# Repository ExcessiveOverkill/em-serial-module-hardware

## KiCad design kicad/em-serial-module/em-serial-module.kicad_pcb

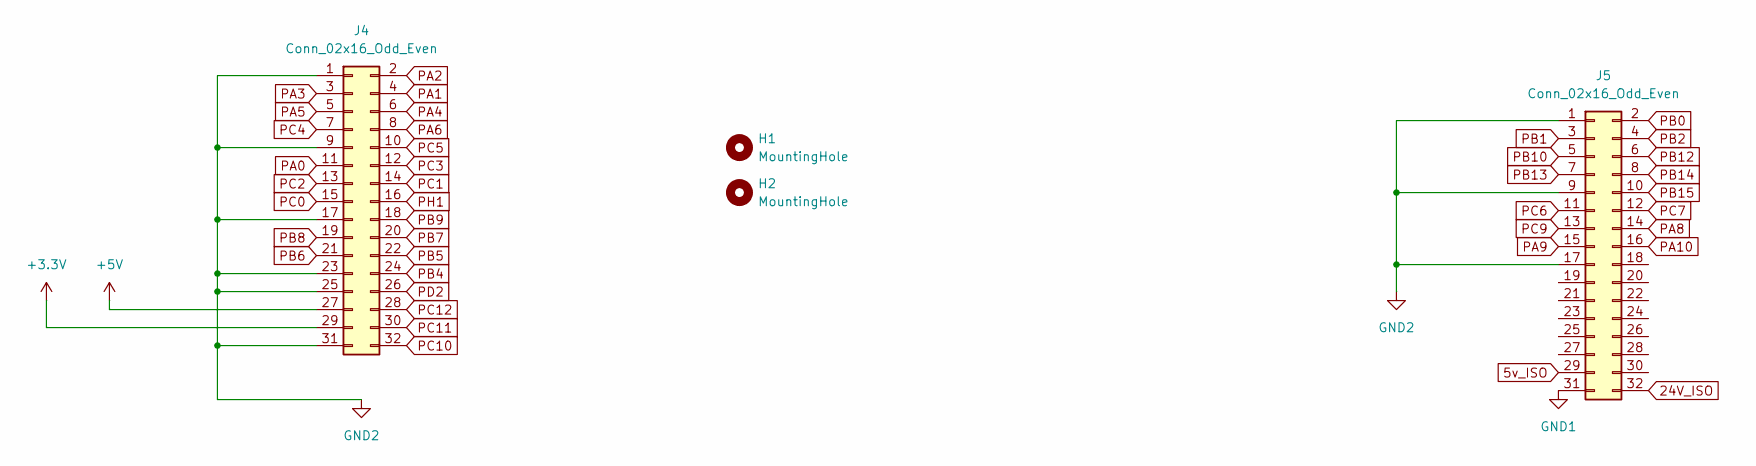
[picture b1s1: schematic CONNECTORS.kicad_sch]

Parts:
H1, H2: MountingHole; MountingHole_3.2mm_M3
J4, J5: Conn_02x16_Odd_Even; PinHeader_2x16_P2.54mm_Vertical

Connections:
5v_ISO: J5.29; also elsewhere on the board
24V_ISO: J5.32; also elsewhere on the board
+3.3V: J4.29; also elsewhere on the board
+5V: J4.27; also elsewhere on the board
GND1: J5.31; also elsewhere on the board
GND2: J4.1, J4.9, J4.17, J4.23, J4.25, J4.31, J5.1, J5.9, J5.17; also elsewhere on the board
PA0: J4.11; also elsewhere on the board
PA1: J4.4; also elsewhere on the board
PA2: J4.2; also elsewhere on the board
PA3: J4.3; also elsewhere on the board
PA4: J4.6; also elsewhere on the board
PA5: J4.5; also elsewhere on the board
PA6: J4.8; also elsewhere on the board
PA8: J5.14; also elsewhere on the board
PA9: J5.15; also elsewhere on the board
PA10: J5.16; also elsewhere on the board
PB0: J5.2; also elsewhere on the board
PB1: J5.3; also elsewhere on the board
PB2: J5.4; also elsewhere on the board
PB4: J4.24; also elsewhere on the board
PB5: J4.22; also elsewhere on the board
PB6: J4.21; also elsewhere on the board
PB7: J4.20; also elsewhere on the board
PB8: J4.19; also elsewhere on the board
PB9: J4.18; also elsewhere on the board
PB10: J5.5; also elsewhere on the board
PB12: J5.6; also elsewhere on the board
PB13: J5.7; also elsewhere on the board
PB14: J5.8; also elsewhere on the board
PB15: J5.10; also elsewhere on the board
PC0: J4.15; also elsewhere on the board
PC1: J4.14; also elsewhere on the board
PC2: J4.13; also elsewhere on the board
PC3: J4.12; also elsewhere on the board
PC4: J4.7; also elsewhere on the board
PC5: J4.10; also elsewhere on the board
PC6: J5.11; also elsewhere on the board
PC7: J5.12; also elsewhere on the board
PC9: J5.13; also elsewhere on the board
PC10: J4.32; also elsewhere on the board
PC11: J4.30; also elsewhere on the board
PC12: J4.28; also elsewhere on the board
PD2: J4.26; also elsewhere on the board
PH1: J4.16; also elsewhere on the board

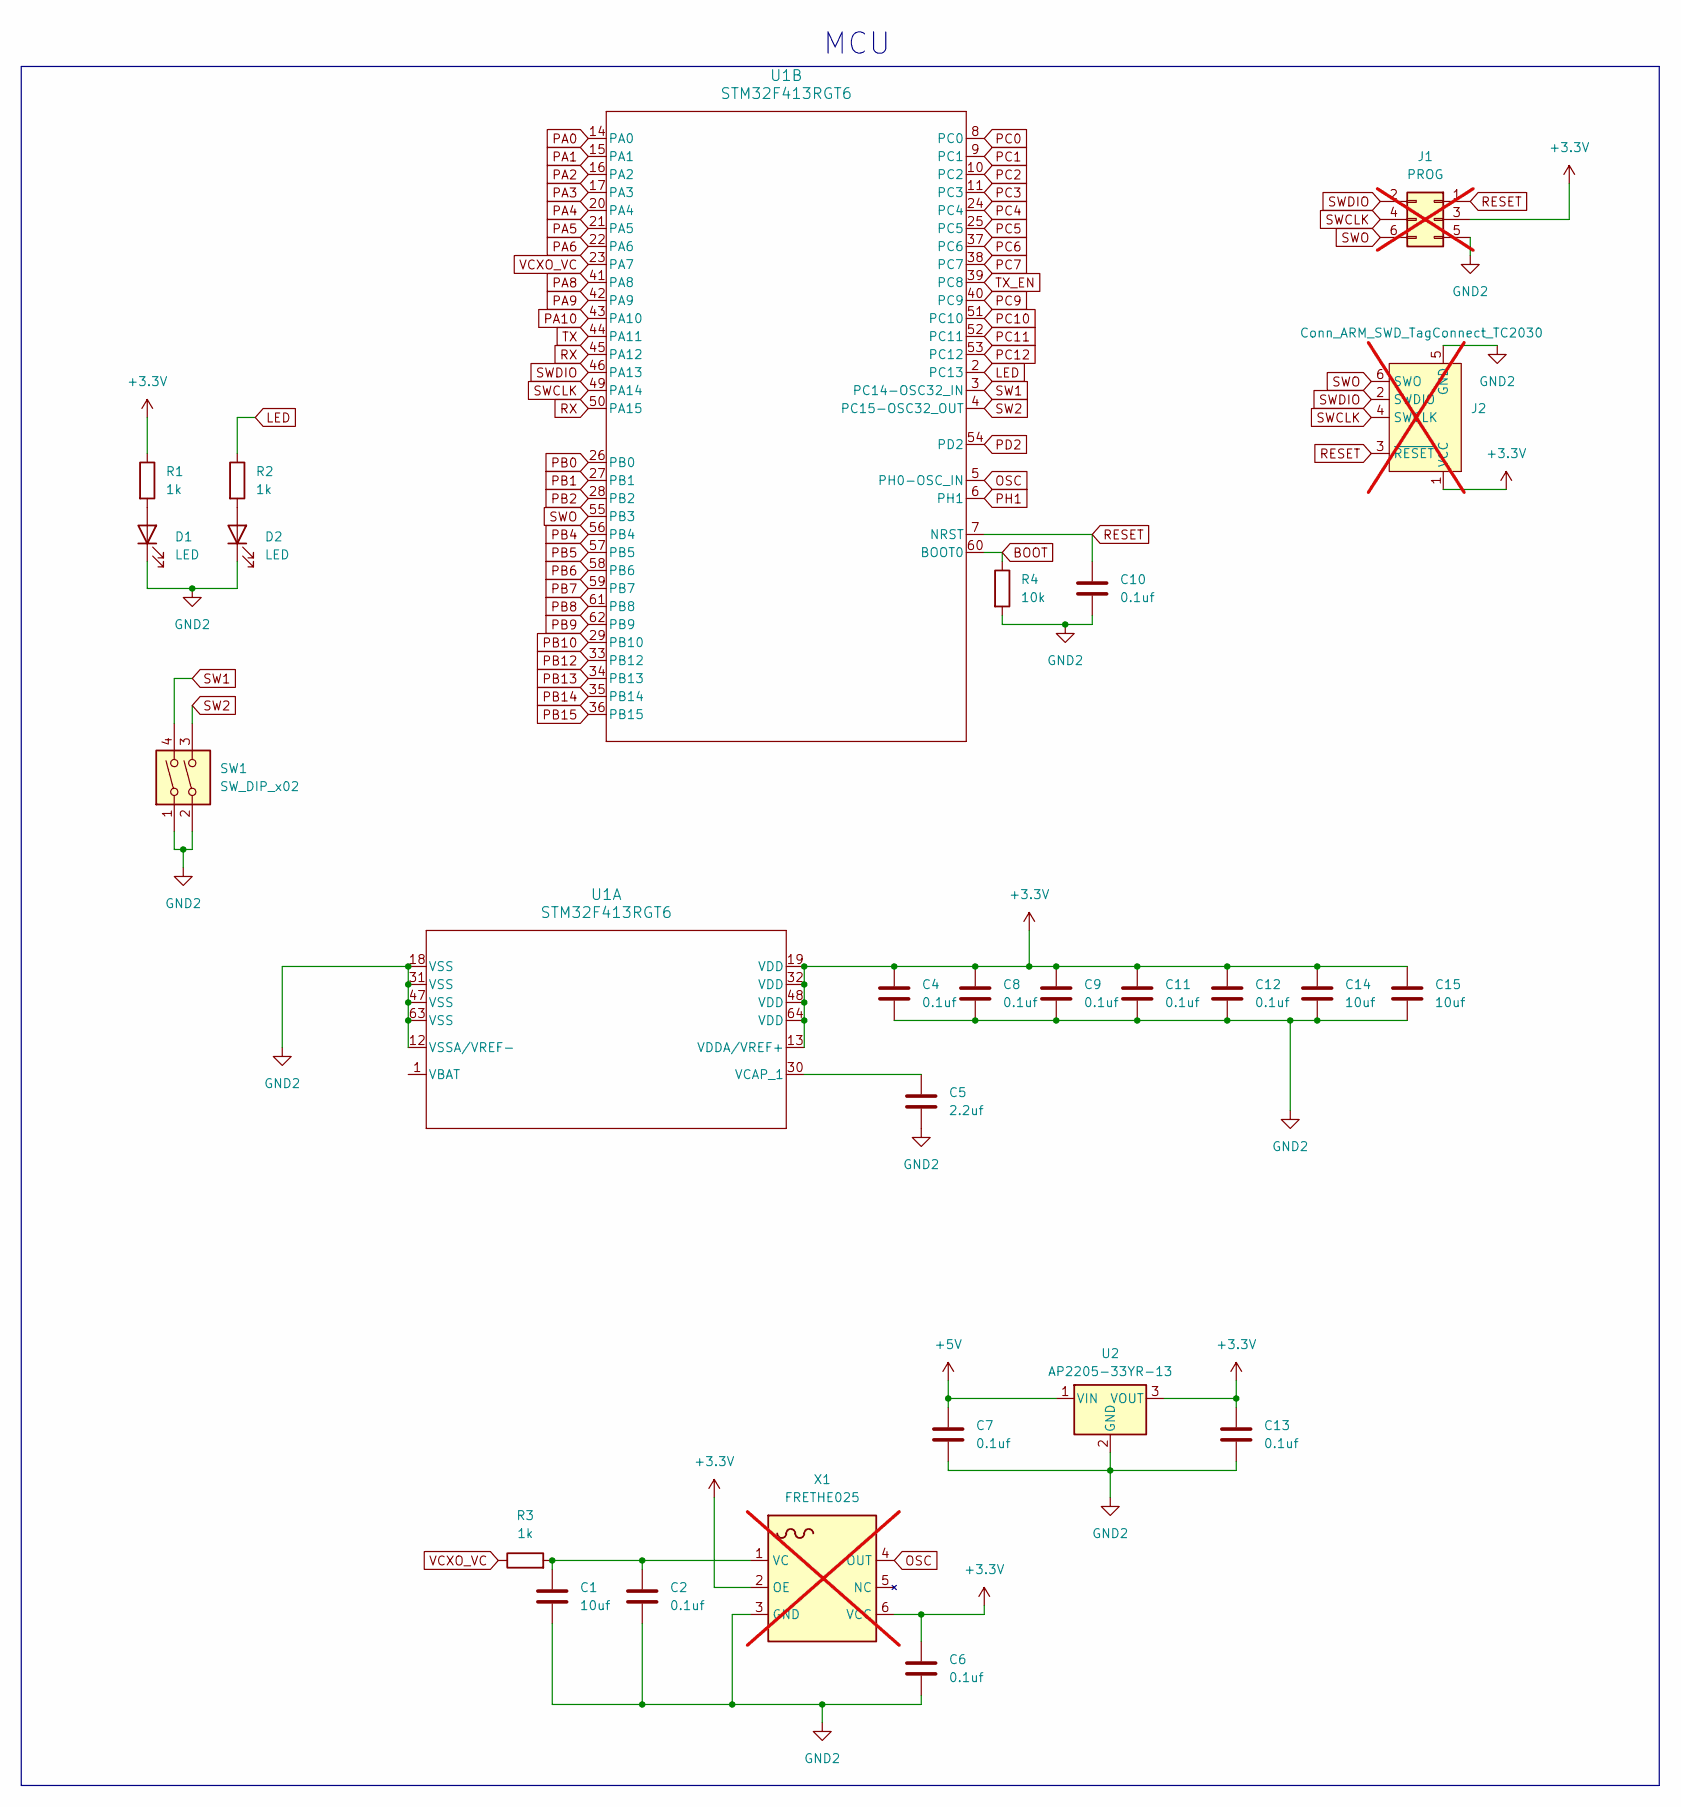
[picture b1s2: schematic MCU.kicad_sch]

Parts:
C1, C14, C15: 10uf; C_0805_2012Metric; Part number GRM21BR61H106KE43L
C2, C4, C6, C7, C8, C9, C10, C11, C12, C13: 0.1uf; C_0603_1608Metric; Part number CC0603ZRY5V9BB104
C5: 2.2uf; C_0603_1608Metric; Part number CL10A105KB8NNNC
D1, D2: LED; LED_0603_1608Metric
J1: PROG; PinHeader_2x03_P2.54mm_Vertical; not fitted
J2: Conn_ARM_SWD_TagConnect_TC2030; Tag-Connect_TC2030-IDC-FP_2x03_P1.27mm_Vertical; not fitted
R1, R2: 1k; R_0603_1608Metric
R3: 1k; R_0603_1608Metric; Part number RC0603FR-071KL
R4: 10k; R_0603_1608Metric; Part number RC0603FR-0710KL
SW1: SW_DIP_x02; DS04-254-2-02BK-SMT_CUD
U1: STM32F413RGT6; LQFP64-10x10mm; Part number STM32F413RGT6
U2: AP2205-33YR-13; SOT-89-3; Part number AP2205-33YR-13
X1: FRETHE025; FR_3-3V; Part number FRETHE025; not fitted

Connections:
+3.3V: C4.1, C6.1, C8.1, C9.1, C11.1, C12.1, C13.1, C14.1, C15.1, J1.3, J2.1 (VCC), R1.1, U1.13 (VDDA/VREF+), U1.19 (VDD), U1.32 (VDD), U1.48 (VDD), U1.64 (VDD), U2.3 (VOUT), X1.2 (OE), X1.6 (VCC); also elsewhere on the board
+5V: C7.1, U2.1 (VIN); also elsewhere on the board
BOOT: R4.1, U1.60 (BOOT0)
GND2: C1.2, C2.2, C4.2, C5.2, C6.2, C7.2, C8.2, C9.2, C10.2, C11.2, C12.2, C13.2, C14.2, C15.2, D1.1 (K), D2.1 (K), J1.5, J2.5 (GND), R4.2, SW1.1, SW1.2, U1.12 (VSSA/VREF-), U1.18 (VSS), U1.31 (VSS), U1.47 (VSS), U1.63 (VSS), U2.2 (GND), X1.3 (GND); also elsewhere on the board
LED: R2.1, U1.2 (PC13)
unnamed: D1.2 (A), R1.2
unnamed: D2.2 (A), R2.2
unnamed: C5.1, U1.30 (VCAP_1)
unnamed: C1.1, C2.1, R3.2, X1.1 (VC)
OSC: U1.5 (PH0-OSC_IN), X1.4 (OUT)
PA0: U1.14 (PA0); also elsewhere on the board
PA1: U1.15 (PA1); also elsewhere on the board
PA2: U1.16 (PA2); also elsewhere on the board
PA3: U1.17 (PA3); also elsewhere on the board
PA4: U1.20 (PA4); also elsewhere on the board
PA5: U1.21 (PA5); also elsewhere on the board
PA6: U1.22 (PA6); also elsewhere on the board
PA8: U1.41 (PA8); also elsewhere on the board
PA9: U1.42 (PA9); also elsewhere on the board
PA10: U1.43 (PA10); also elsewhere on the board
PB0: U1.26 (PB0); also elsewhere on the board
PB1: U1.27 (PB1); also elsewhere on the board
PB2: U1.28 (PB2); also elsewhere on the board
PB4: U1.56 (PB4); also elsewhere on the board
PB5: U1.57 (PB5); also elsewhere on the board
PB6: U1.58 (PB6); also elsewhere on the board
PB7: U1.59 (PB7); also elsewhere on the board
PB8: U1.61 (PB8); also elsewhere on the board
PB9: U1.62 (PB9); also elsewhere on the board
PB10: U1.29 (PB10); also elsewhere on the board
PB12: U1.33 (PB12); also elsewhere on the board
PB13: U1.34 (PB13); also elsewhere on the board
PB14: U1.35 (PB14); also elsewhere on the board
PB15: U1.36 (PB15); also elsewhere on the board
PC0: U1.8 (PC0); also elsewhere on the board
PC1: U1.9 (PC1); also elsewhere on the board
PC2: U1.10 (PC2); also elsewhere on the board
PC3: U1.11 (PC3); also elsewhere on the board
PC4: U1.24 (PC4); also elsewhere on the board
PC5: U1.25 (PC5); also elsewhere on the board
PC6: U1.37 (PC6); also elsewhere on the board
PC7: U1.38 (PC7); also elsewhere on the board
PC9: U1.40 (PC9); also elsewhere on the board
PC10: U1.51 (PC10); also elsewhere on the board
PC11: U1.52 (PC11); also elsewhere on the board
PC12: U1.53 (PC12); also elsewhere on the board
PD2: U1.54 (PD2); also elsewhere on the board
PH1: U1.6 (PH1); also elsewhere on the board
RESET: C10.1, J1.1, J2.3 (~RESET), U1.7 (NRST)
RX: U1.45 (PA12), U1.50 (PA15); also elsewhere on the board
SW1: SW1.4, U1.3 (PC14-OSC32_IN)
SW2: SW1.3, U1.4 (PC15-OSC32_OUT)
SWCLK: J1.4, J2.4 (SWCLK), U1.49 (PA14)
SWDIO: J1.2, J2.2 (SWDIO), U1.46 (PA13)
SWO: J1.6, J2.6 (SWO), U1.55 (PB3)
TX: U1.44 (PA11); also elsewhere on the board
TX_EN: U1.39 (PC8); also elsewhere on the board
VCXO_VC: R3.1, U1.23 (PA7)

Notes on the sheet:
MCU

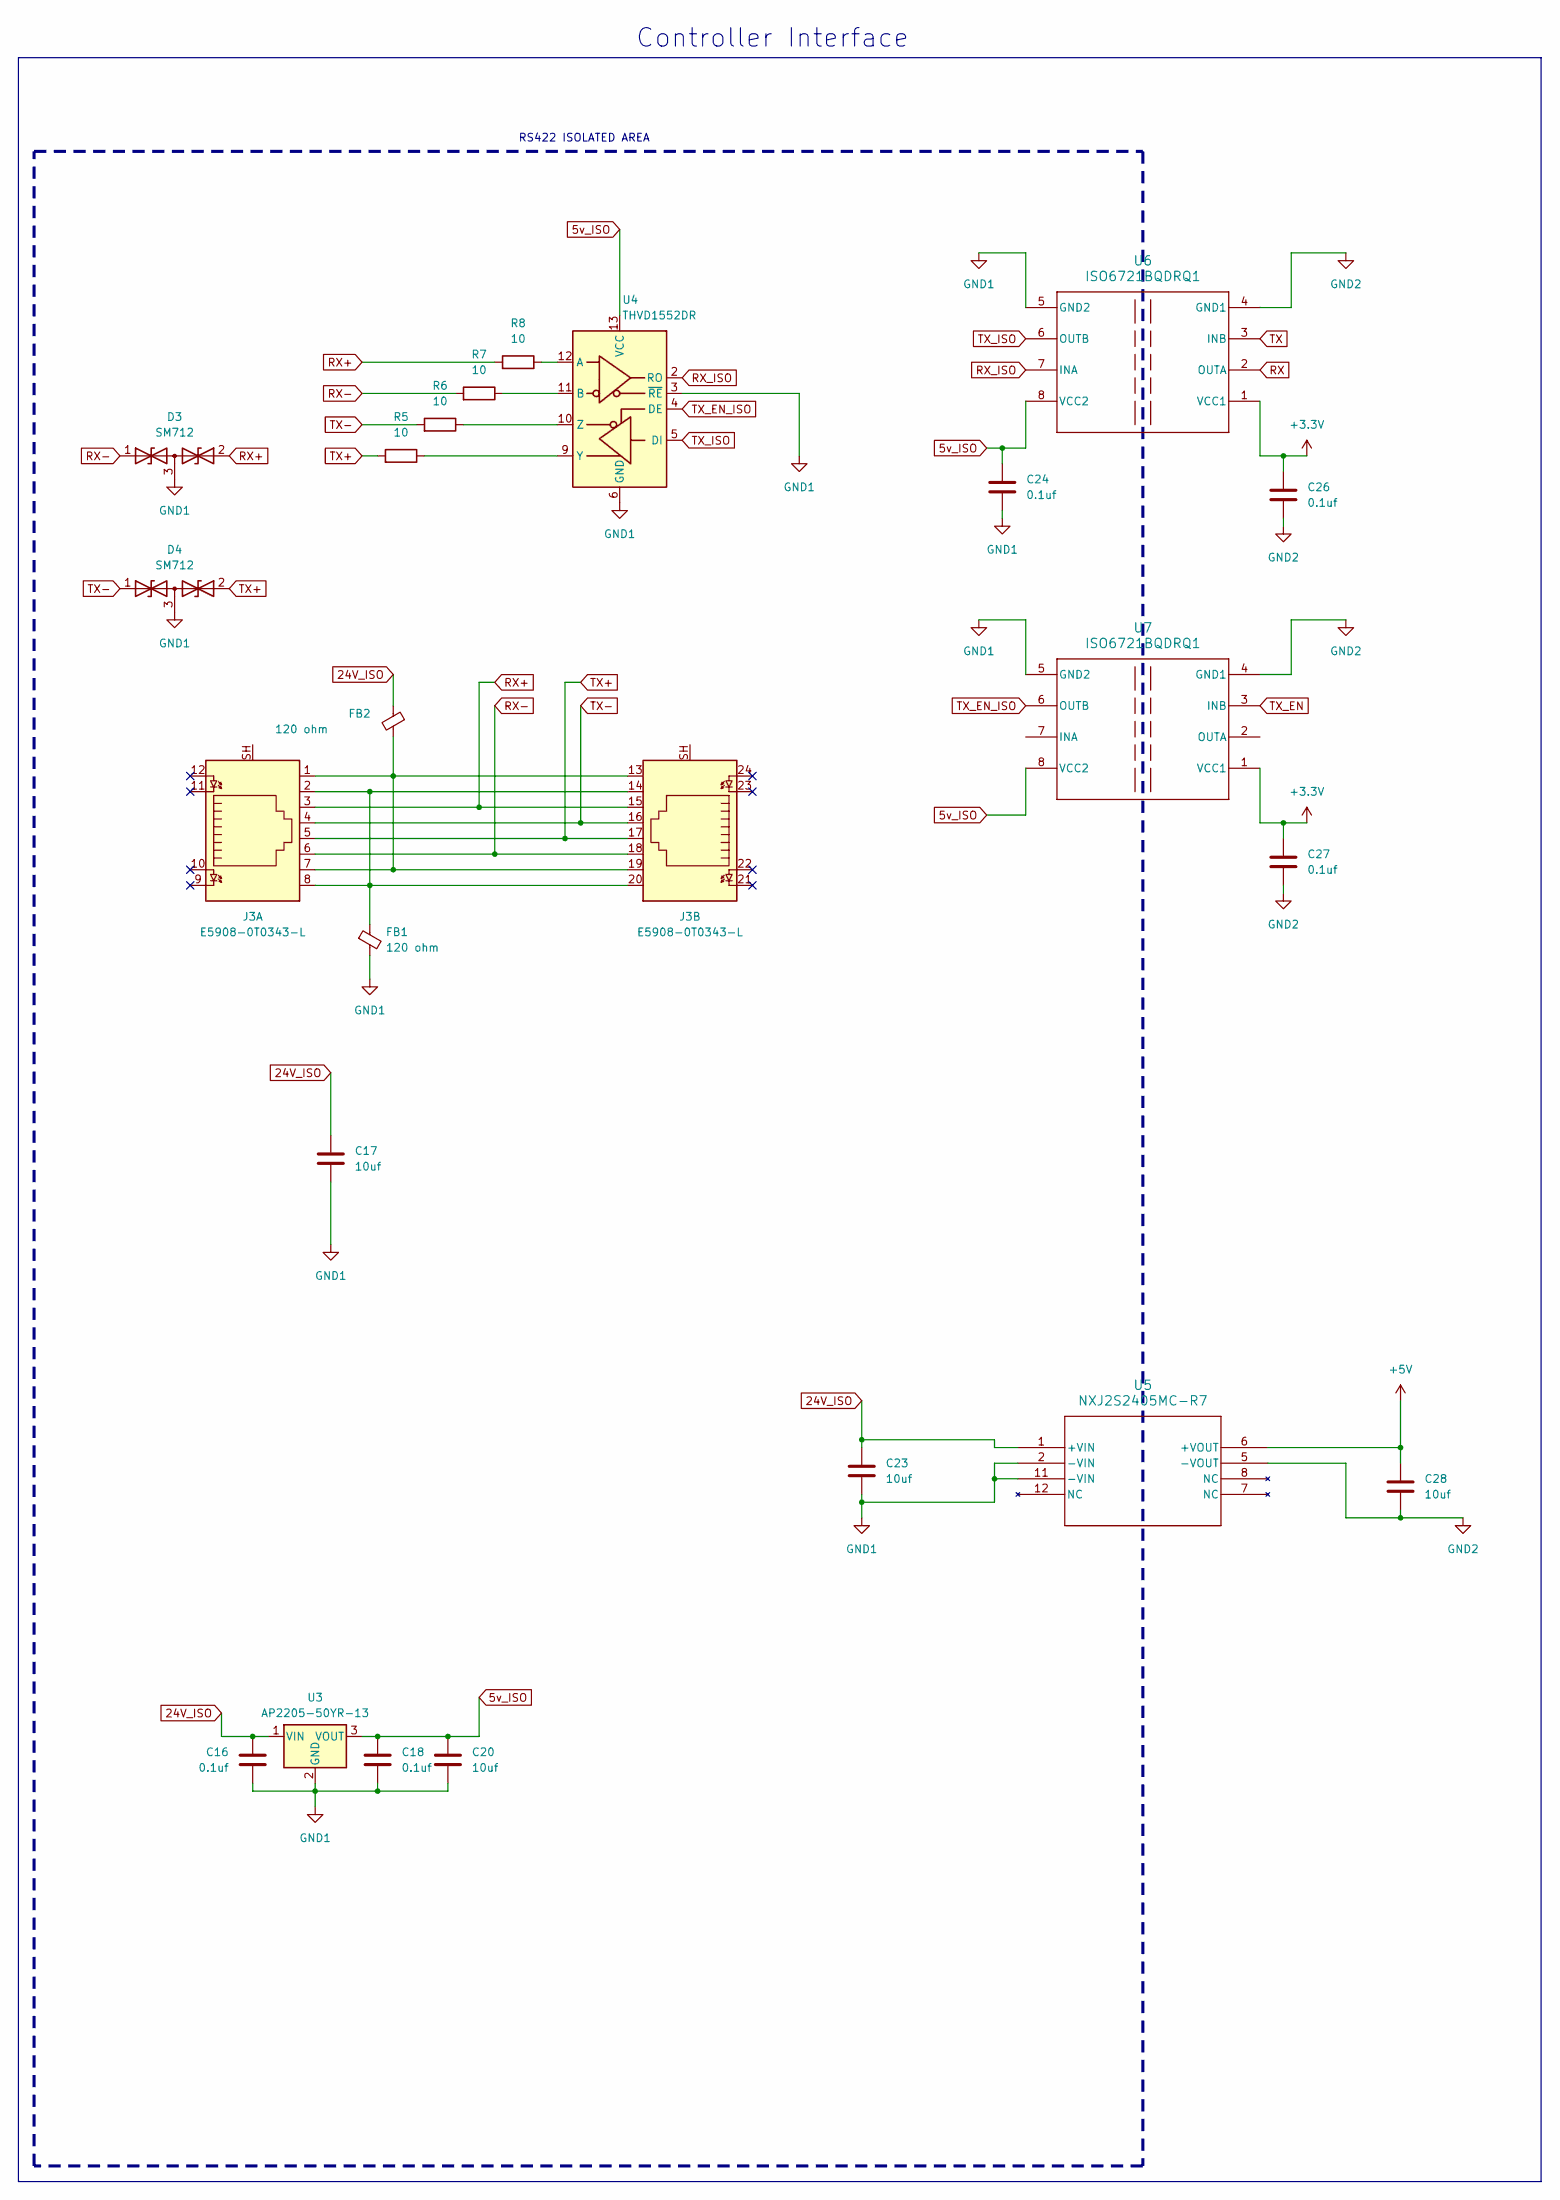
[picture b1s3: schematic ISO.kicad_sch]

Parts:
C16, C18, C24, C26, C27: 0.1uf; C_0603_1608Metric; Part number CC0603ZRY5V9BB104
C17, C20, C23, C28: 10uf; C_0805_2012Metric; Part number GRM21BR61H106KE43L
D3, D4: SM712; SOT-23; Part number SM712
FB1, FB2: 120 ohm; L_0603_1608Metric; Part number LI0603G121R-10
J3: E5908-0T0343-L; RJ45_E5908-0T0343-L; Part number E5908-0T0343-L
R5, R6, R7, R8: 10; R_0603_1608Metric; Part number RMCF0603FT10R0
U3: AP2205-50YR-13; SOT-89-3; Part number AP2205-50YR-13
U4: THVD1552DR; SOIC-14_3.9x8.7mm_P1.27mm; Part number THVD1552DR
U5: NXJ2S2405MC-R7; NXJ2_24V_MUR; Part number NXJ2S2415MC-R7
U6, U7: ISO6721BQDRQ1; SOICN-8_LTF; Part number ISO6721BQDRQ1

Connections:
5v_ISO: C18.2, C20.1, C24.1, U3.3 (VOUT), U4.13 (VCC), U4.14 (VCC), U6.8 (VCC2), U7.8 (VCC2); also elsewhere on the board
24V_ISO: C16.1, C17.1, C23.1, FB2.1, U3.1 (VIN), U5.1 (+VIN); also elsewhere on the board
+3.3V: C26.1, C27.1, U6.1 (VCC1), U7.1 (VCC1); also elsewhere on the board
+5V: C28.1, U5.6 (+VOUT); also elsewhere on the board
GND1: C16.2, C17.2, C18.1, C20.2, C23.2, C24.2, D3.3 (common), D4.3 (common), FB1.2, U3.2 (GND), U4.3 (~RE), U4.6 (GND), U4.7 (GND), U5.2 (-VIN), U5.11 (-VIN), U6.5 (GND2), U7.5 (GND2); also elsewhere on the board
GND2: C26.2, C27.2, C28.2, U5.5 (-VOUT), U6.4 (GND1), U7.4 (GND1); also elsewhere on the board
unnamed: FB1.1, J3.2, J3.8, J3.14, J3.20
unnamed: FB2.2, J3.1, J3.7, J3.13, J3.19
unnamed: R8.1, U4.12 (A)
unnamed: R7.1, U4.11 (B)
unnamed: R5.1, U4.9 (Y)
unnamed: R6.1, U4.10 (Z)
RX: U6.2 (OUTA); also elsewhere on the board
RX+: D3.2 (A2), J3.3, J3.15, R8.2
RX-: D3.1 (A1), J3.6, J3.18, R7.2
RX_ISO: U4.2 (RO), U6.7 (INA)
TX: U6.3 (INB); also elsewhere on the board
TX+: D4.2 (A2), J3.5, J3.17, R5.2
TX-: D4.1 (A1), J3.4, J3.16, R6.2
TX_EN: U7.3 (INB); also elsewhere on the board
TX_EN_ISO: U4.4 (DE), U7.6 (OUTB)
TX_ISO: U4.5 (DI), U6.6 (OUTB)

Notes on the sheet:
RS422 ISOLATED AREA
Controller Interface

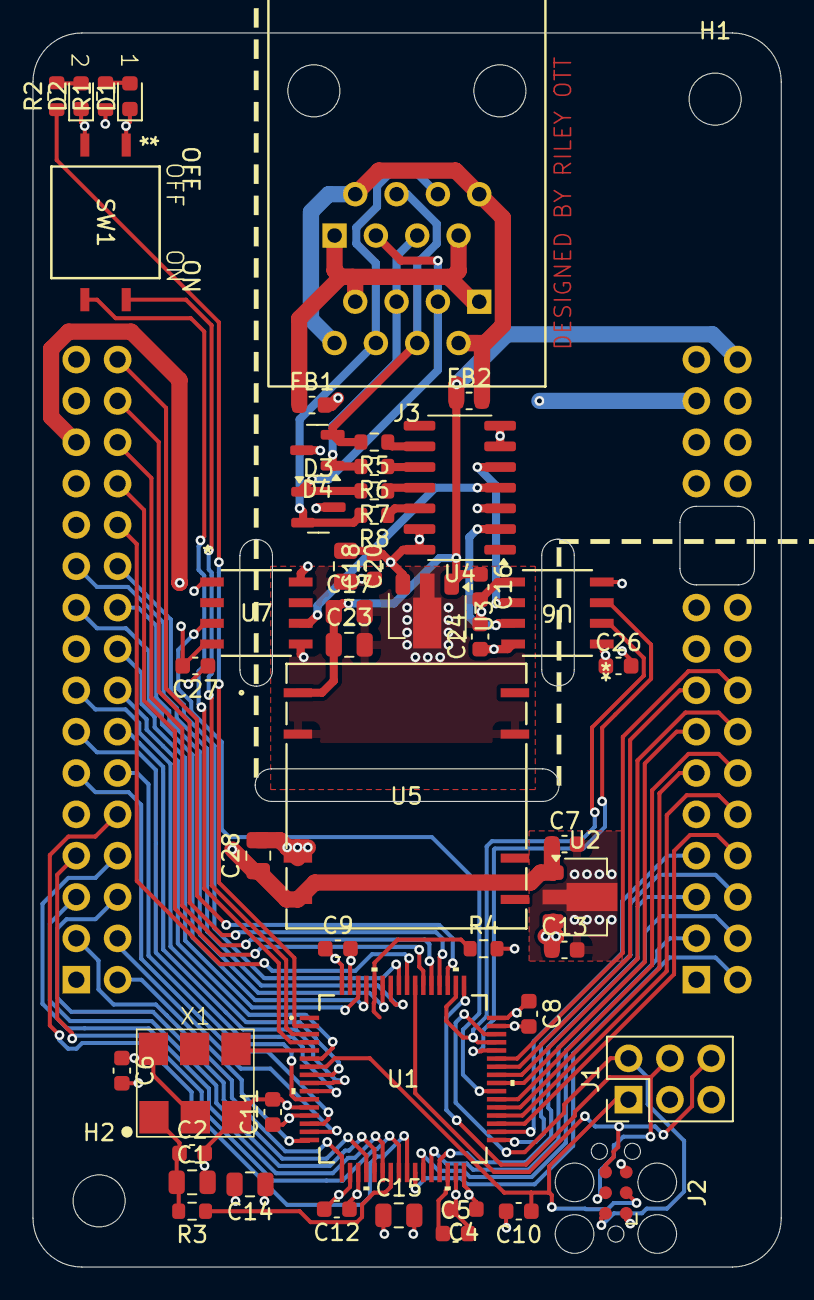
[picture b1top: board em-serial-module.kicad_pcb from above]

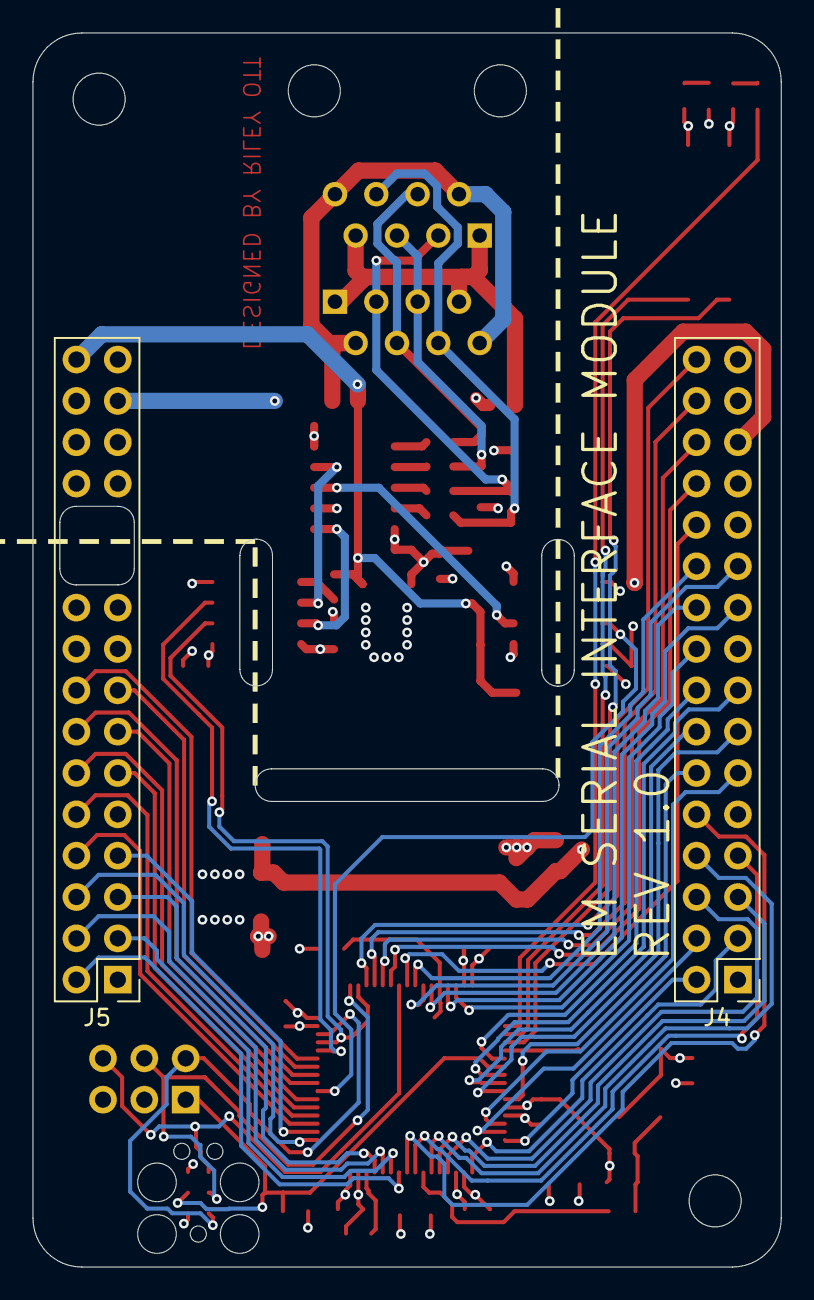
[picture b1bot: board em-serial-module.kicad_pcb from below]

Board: 4 copper layers, 46.0 x 75.8 mm, 53 parts (2 on the bottom side), 74 nets.
